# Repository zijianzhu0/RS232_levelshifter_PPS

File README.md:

# RS232_levelshifter_PPS
RS232 level shifter with PPS for ublox. 

This level shifter is made for 1 serial port with TX, RX and a PPS signal.

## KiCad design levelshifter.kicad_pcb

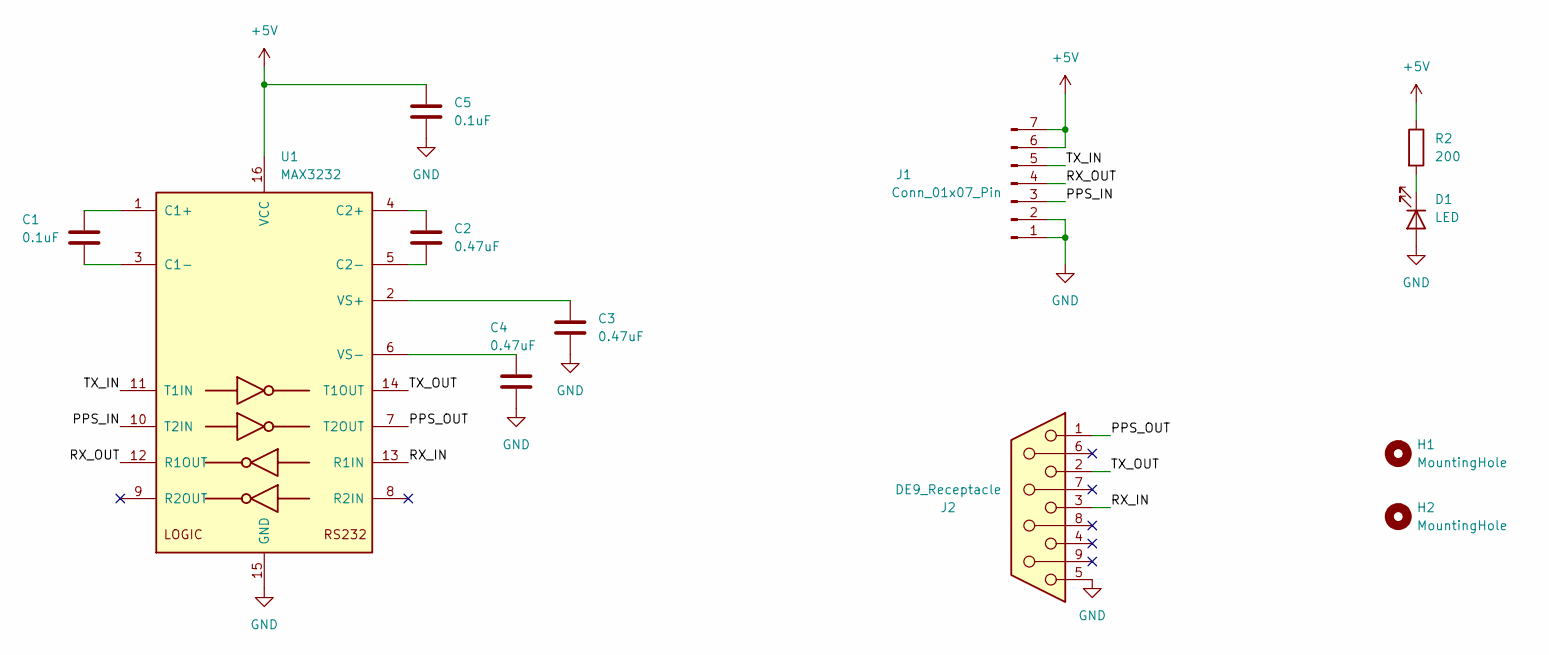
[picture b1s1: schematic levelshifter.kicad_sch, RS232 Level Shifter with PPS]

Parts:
C1, C5: 0.1uF; C_0805_2012Metric_Pad1.18x1.45mm_HandSolder
C2, C3, C4: 0.47uF; C_0805_2012Metric_Pad1.18x1.45mm_HandSolder
D1: LED; LED_0805_2012Metric_Pad1.15x1.40mm_HandSolder
H1, H2: MountingHole; MountingHole_3.2mm_M3_ISO7380
J1: Conn_01x07_Pin; PinHeader_1x07_P2.54mm_Vertical
J2: DE9_Receptacle; DSUB-9_Female_Horizontal_P2.77x2.84mm_EdgePinOffset9.90mm_H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
R2: 200; R_0805_2012Metric_Pad1.20x1.40mm_HandSolder
U1: MAX3232; SOIC-16_3.9x9.9mm_P1.27mm

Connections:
+5V: C5.1, J1.6, J1.7, R2.1, U1.16 (VCC)
/PPS_IN: J1.3, U1.10 (T2IN)
/PPS_OUT: J2.1, U1.7 (T2OUT)
/RX_IN: J2.3, U1.13 (R1IN)
/RX_OUT: J1.4, U1.12 (R1OUT)
/TX_IN: J1.5, U1.11 (T1IN)
/TX_OUT: J2.2, U1.14 (T1OUT)
GND: C3.2, C4.2, C5.2, D1.2 (A), J1.1, J1.2, J2.5, U1.15 (GND)
unnamed: D1.1 (K), R2.2
unnamed: C1.1, U1.1 (C1+)
unnamed: C1.2, U1.3 (C1-)
unnamed: C2.1, U1.4 (C2+)
unnamed: C2.2, U1.5 (C2-)
unnamed: C3.1, U1.2 (VS+)
unnamed: C4.1, U1.6 (VS-)

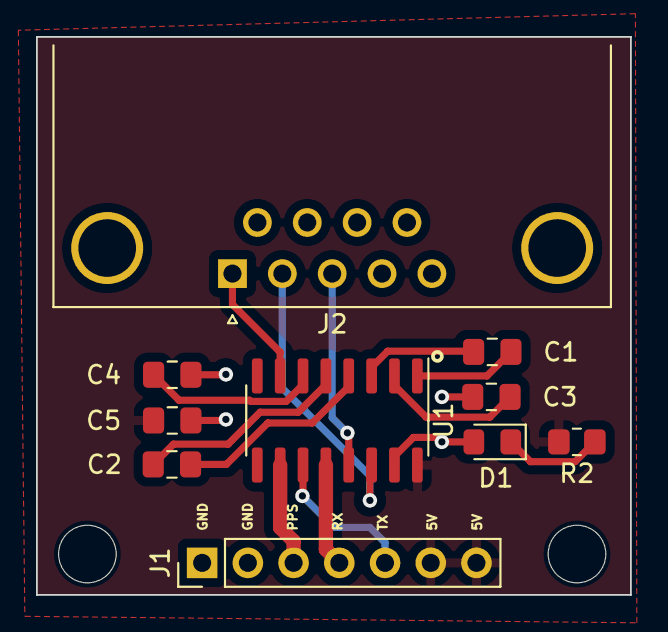
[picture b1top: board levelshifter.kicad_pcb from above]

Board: 2 copper layers, 33.0 x 31.0 mm, 12 parts (0 on the bottom side), 15 nets.

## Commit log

2024-12-25 updated gitignore, removed fab files
